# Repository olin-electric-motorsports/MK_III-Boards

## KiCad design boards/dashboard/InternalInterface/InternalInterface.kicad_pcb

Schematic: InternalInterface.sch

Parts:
J1: micromatch_female_TOP_ENTRY_locking_10; micromatch_female_vert_10; MPN A99504CT-ND
J2, J3: Ultrafit_2; MPN WM11570-ND
J4, J5, J6: Ultrafit_4; MPN WM11574-ND
R1: R_200; R_0805_OEM; MPN RMCF0805JT200RCT-ND

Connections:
+5V: J1.1, J1.8, J4.1, J5.1, J6.1, R1.2
AMS: J1.4, J2.1
GND: J1.2, J1.5, J1.7, J2.2, J3.2, J4.2, J5.2, J6.4
IMD: J1.6, J3.1
unnamed: J6.3, R1.1
SCL: J1.10, J4.4, J5.4
SDA: J1.9, J4.3, J5.3
START: J1.3, J6.2

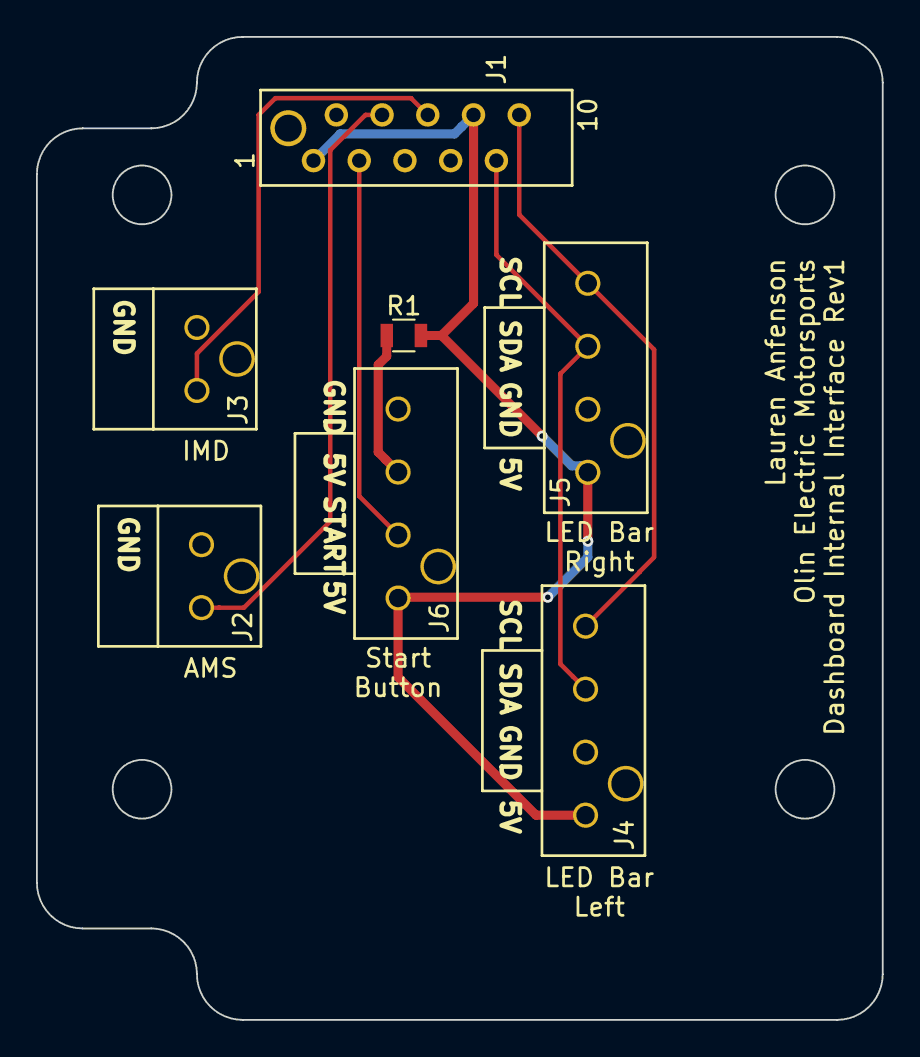
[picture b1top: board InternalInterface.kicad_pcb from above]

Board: 2 copper layers, 47.0 x 54.6 mm, 7 parts (0 on the bottom side), 8 nets.

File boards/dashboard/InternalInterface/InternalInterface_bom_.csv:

Component,Description,Part,References,Value,Footprint,Quantity Per PCB,Datasheet,Package,MPN,MFN,PurchasingLink,PurchasingLink2,MPN2
1,ULTRAFIT CONN HDR 02CKT,Ultrafit_2,J2 J3,Ultrafit_2,Ultrafit_2,2,,Value,WM11570-ND,Digi-Key,https://www.digikey.com/product-detail/en/molex-llc/17228611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,,
2,Ultrafit 4 Pin Connector,Ultrafit_4,J4 J5 J6,Ultrafit_4,Ultrafit_4,3,http://www.literature.molex.com/SQLImages/kelmscott/Molex/PD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,Value,WM11574-ND,Digi-Key,https://www.digikey.com/products/en?keywords=WM11574-ND,https://www.digikey.com/product-detail/en/molex-llc/17225610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,WM11564-ND
3,CONN FMALE-ON-BRD 10POS VERT T/H,micromatch_female_TOP_ENTRY_locking_10,J1,micromatch_female_TOP_ENTRY_locking_10,micromatch_female_vert_10,1,http://www.te.com/commerce/DocumentDelivery/DDEController?Ac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,Value,A99504CT-ND,Digi-Key,https://www.digikey.com/product-detail/en/te-connectivity-am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,,
4,Res 200 5%,R_200,R1,R_200,R_0805_OEM,1,https://www.seielect.com/Catalog/SEI-RMCF_RMCP.pdf,Value,RMCF0805JT200RCT-ND,Digi-Key,https://www.digikey.com/products/en?keywords=RMCF0805JT200RCT-ND,,





Component Groups:,4
Component Count:,7
Fitted Components:,7
Number of PCBs:,1
Total components:,7
Schematic Version:,
Schematic Date:,
BoM Date:,Wed 21 Feb 2018 10:05:45 PM EST
Schematic Source:,/home/lanfenson/MK_III-Boards-master/boards/dashboard/InternalInterface/InternalInterface.sch
KiCad Version:,Eeschema 4.0.7-e2-6376~58~ubuntu16.04.1

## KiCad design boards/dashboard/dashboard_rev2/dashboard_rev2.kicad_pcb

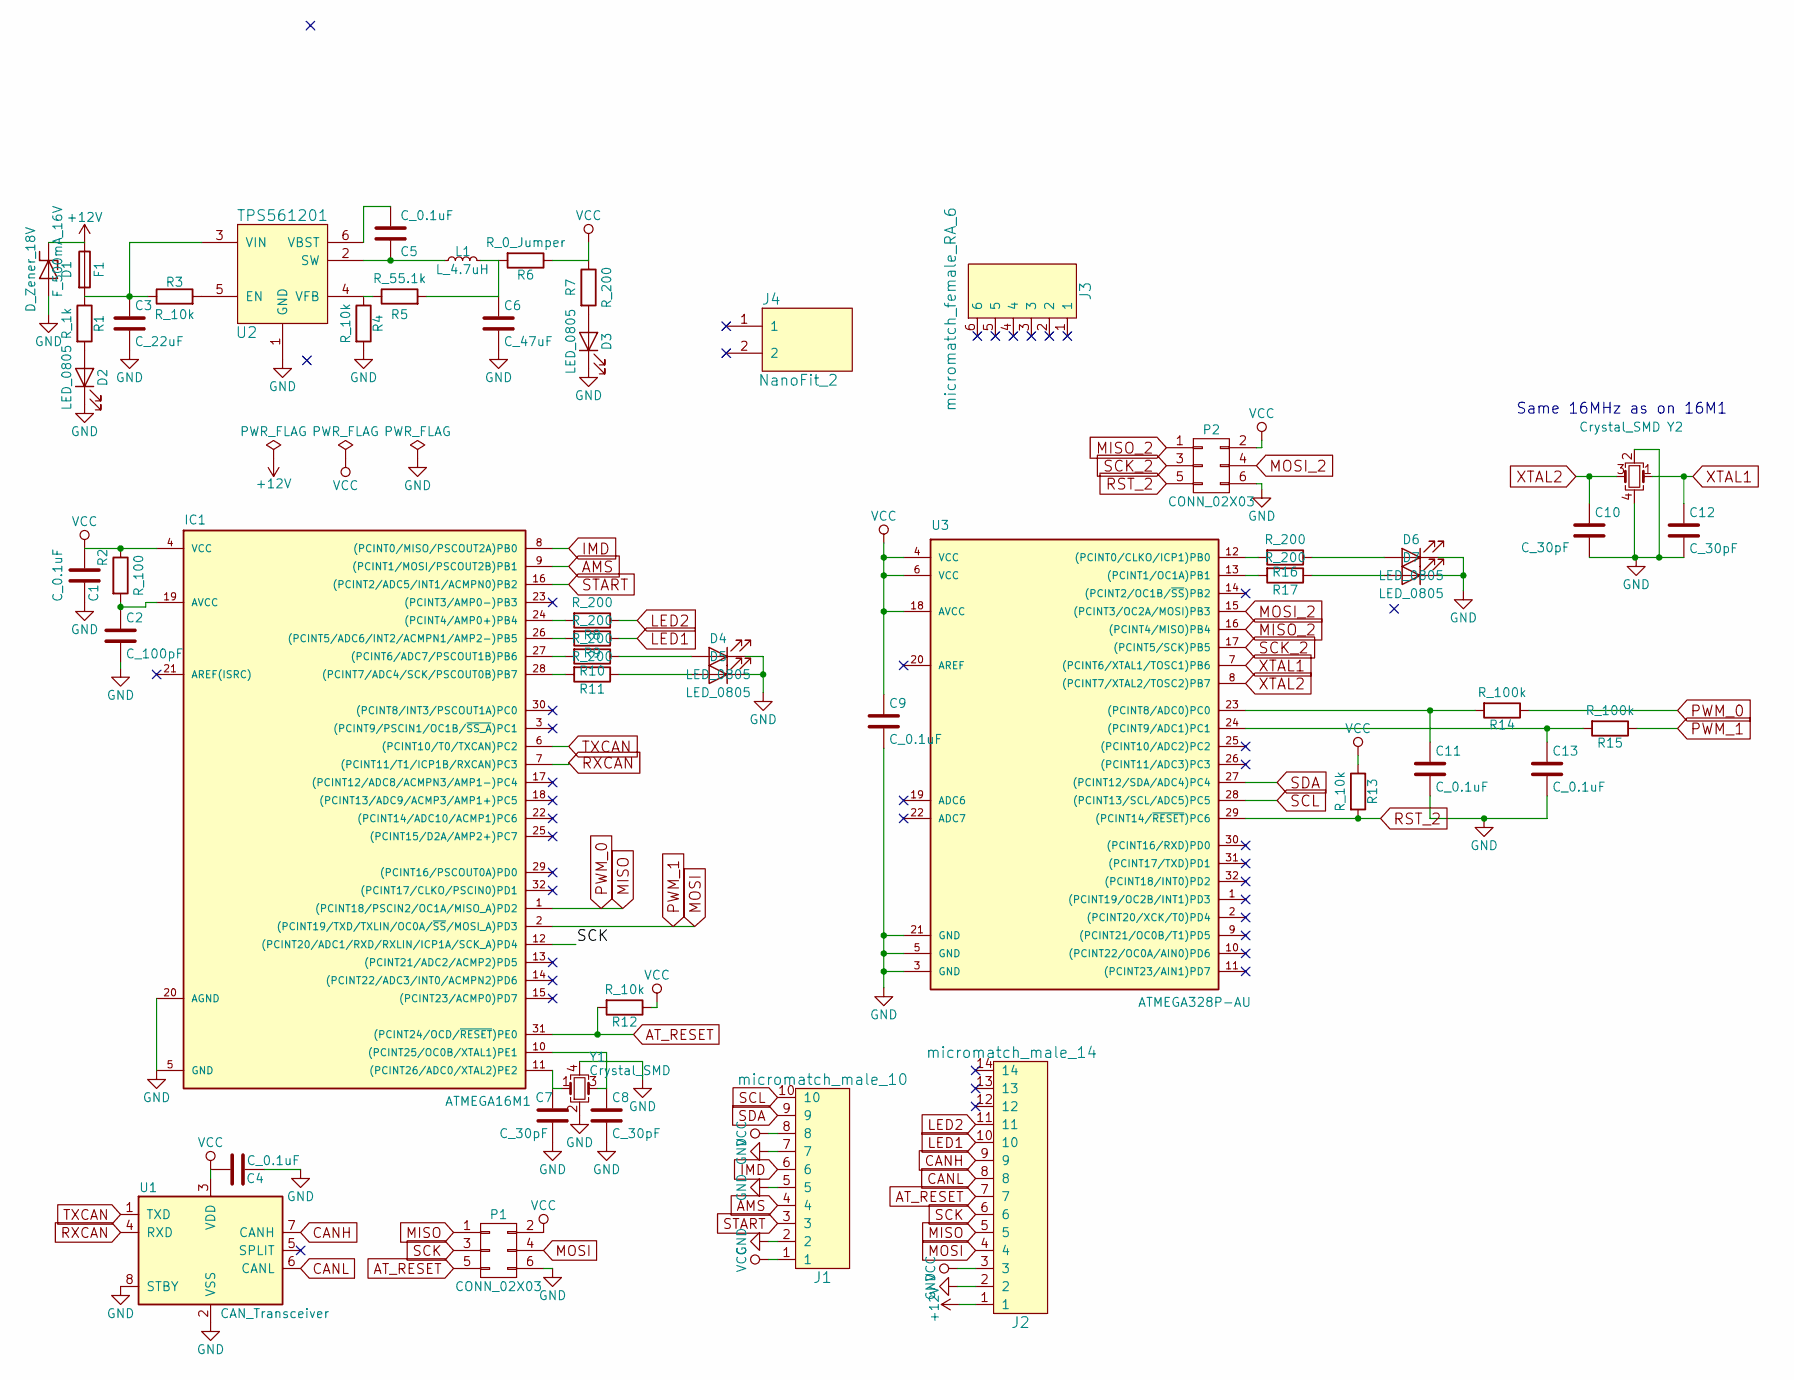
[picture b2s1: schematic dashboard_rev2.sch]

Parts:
C1, C4, C5: C_0.1uF; C_0805; MPN 478-3352-1-ND
C2: C_100pF; C_0805; MPN 399-1122-1-ND
C3: C_22uF; C_1206; MPN 1276-2725-1-ND
C6: C_47uF; C_0805; MPN 587-4280-1-ND
C7, C8: C_30pF; C_0805; MPN 1276-1130-1-ND
C9, C11, C13: C_0.1uF; C_0805_OEM; MPN 478-3352-1-ND
C10, C12: C_30pF; C_0805_OEM; MPN 1276-1130-1-ND
D1: D_Zener_18V; DO-214AA; MPN SMBJ5355B-TPMSCT-ND
D2, D3, D4, D5, D6, D7: LED_0805; MPN 475-1410-1-ND
F1: F_500mA_16V; Fuse_1210; MPN 507-1786-1-ND
IC1: ATMEGA16M1; TQFP-32_7x7mm_Pitch0.8mm; MPN ATMEGA16M1-AU-ND
J1: micromatch_male_10; micromatch_female_ra_10; MPN A110881CT-ND
J2: micromatch_male_14; micromatch_female_ra_14; MPN A99442CT-ND
J3: micromatch_female_RA_6; micromatch_female_ra_6; MPN A99483CT-ND
J4: NanoFit_2; OLIN_O
L1: L_4.7uH; 4.7uH_Inductor_OEM; MPN 445-6583-1-ND
P1, P2: CONN_02X03; Pin_Header_Straight_2x03; MPN 609-3234-ND
R1: R_1k; R_0805_OEM; MPN RNCP0805FTD1K00CT-ND
R2: R_100; R_0805; MPN RNCP0805FTD100RCT-ND
R3, R4, R12: R_10k; R_0805; MPN CRS0805-FX-1002ELFCT-ND
R5: R_55.1k; R_0805; MPN 311-51.1KCRCT-ND
R6: R_0_Jumper; R_2512; MPN A121322CT-ND
R7: R_200; R_0805; MPN RMCF0805JT200RCT-ND
R8, R9, R10, R11, R16, R17: R_200; R_0805_OEM; MPN RMCF0805JT200RCT-ND
R13: R_10k; R_0805_OEM; MPN CRS0805-FX-1002ELFCT-ND
R14, R15: R_100k; R_0805_OEM; MPN 311-100KCRCT-ND
U1: CAN_Transceiver; SOIC-8_3.9x4.9mm_Pitch1.27mm; MPN MCP2561-E/SN-ND
U2: TPS561201; SOT-23-6; MPN TPS561201
U3: ATMEGA328P-AU; TQFP-32_7x7mm_Pitch0.8mm
Y1, Y2: Crystal_SMD; Crystal_SMD_FA238; MPN SER3686CT-ND

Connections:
+12V: D1.1 (K), F1.1, J2.1
AMS: IC1.9 ((PCINT1/MOSI/PSCOUT2B)PB1), J1.4
AT_RESET: IC1.31 ((PCINT24/OCD/~RESET~)PE0), J2.7, P1.5, R12.2
CANH: J2.9, U1.7 (CANH)
CANL: J2.8, U1.6 (CANL)
GND: C1.2, C2.2, C3.2, C4.2, C6.2, C7.2, C8.2, C9.2, C10.2, C11.2, C12.2, C13.2, D1.2 (A), D2.1 (K), D3.1 (K), D4.1 (K), D5.1 (K), D6.1 (K), D7.1 (K), IC1.5 (GND), IC1.20 (AGND), J1.2, J1.5, J1.7, J2.2, P1.6, P2.6, R4.2, U1.2 (VSS), U1.8 (STBY), U2.1 (GND), U3.3 (GND), U3.5 (GND), U3.21 (GND), Y1.2, Y1.4, Y2.2, Y2.4
IMD: IC1.8 ((PCINT0/MISO/PSCOUT2A)PB0), J1.6
LED1: J2.10, R9.1
LED2: J2.11, R8.1
MISO: IC1.1 ((PCINT18/PSCIN2/OC1A/MISO_A)PD2), J2.5, P1.1, R14.1
MISO_2: P2.1, U3.16 ((PCINT4/MISO)PB4)
MOSI: IC1.2 ((PCINT19/TXD/TXLIN/OC0A/~SS~/MOSI_A)PD3), J2.4, P1.4, R15.1
MOSI_2: P2.4, U3.15 ((PCINT3/OC2A/MOSI)PB3)
unnamed: C2.1, IC1.19 (AVCC), R2.2
unnamed: C3.1, F1.2, R1.1, R3.1, U2.3 (VIN)
unnamed: C5.1, U2.6 (VBST)
unnamed: C5.2, L1.1, U2.2 (SW)
unnamed: C6.1, L1.2, R5.2, R6.2
unnamed: C7.1, IC1.11 ((PCINT26/ADC0/XTAL2)PE2), Y1.1
unnamed: C8.1, IC1.10 ((PCINT25/OC0B/XTAL1)PE1), Y1.3
unnamed: C11.1, R14.2, U3.23 ((PCINT8/ADC0)PC0)
unnamed: C13.1, R15.2, U3.24 ((PCINT9/ADC1)PC1)
unnamed: D2.2 (A), R1.2
unnamed: D3.2 (A), R7.2
unnamed: D4.2 (A), R10.1
unnamed: D5.2 (A), R11.1
unnamed: D6.2 (A), R16.1
unnamed: D7.2 (A), R17.1
unnamed: IC1.24 ((PCINT4/AMP0+)PB4), R8.2
unnamed: IC1.26 ((PCINT5/ADC6/INT2/ACMPN1/AMP2-)PB5), R9.2
unnamed: IC1.27 ((PCINT6/ADC7/PSCOUT1B)PB6), R10.2
unnamed: IC1.28 ((PCINT7/ADC4/SCK/PSCOUT0B)PB7), R11.2
unnamed: R3.2, U2.5 (EN)
unnamed: R4.1, R5.1, U2.4 (VFB)
unnamed: R16.2, U3.12 ((PCINT0/CLKO/ICP1)PB0)
unnamed: R17.2, U3.13 ((PCINT1/OC1A)PB1)
RST_2: P2.5, R13.2, U3.29 ((PCINT14/~RESET~)PC6)
RXCAN: IC1.7 ((PCINT11/T1/ICP1B/RXCAN)PC3), U1.4 (RXD)
SCK: IC1.12 ((PCINT20/ADC1/RXD/RXLIN/ICP1A/SCK_A)PD4), J2.6, P1.3
SCK_2: P2.3, U3.17 ((PCINT5/SCK)PB5)
SCL: J1.10, U3.28 ((PCINT13/SCL/ADC5)PC5)
SDA: J1.9, U3.27 ((PCINT12/SDA/ADC4)PC4)
START: IC1.16 ((PCINT2/ADC5/INT1/ACMPN0)PB2), J1.3
TXCAN: IC1.6 ((PCINT10/T0/TXCAN)PC2), U1.1 (TXD)
VCC: C1.1, C4.1, C9.1, IC1.4 (VCC), J1.1, J1.8, J2.3, P1.2, P2.2, R2.1, R6.1, R7.1, R12.1, R13.1, U1.3 (VDD), U3.4 (VCC), U3.6 (VCC), U3.18 (AVCC)
XTAL1: C12.1, U3.7 ((PCINT6/XTAL1/TOSC1)PB6), Y2.1
XTAL2: C10.1, U3.8 ((PCINT7/XTAL2/TOSC2)PB7), Y2.3

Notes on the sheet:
Same 16MHz as on 16M1

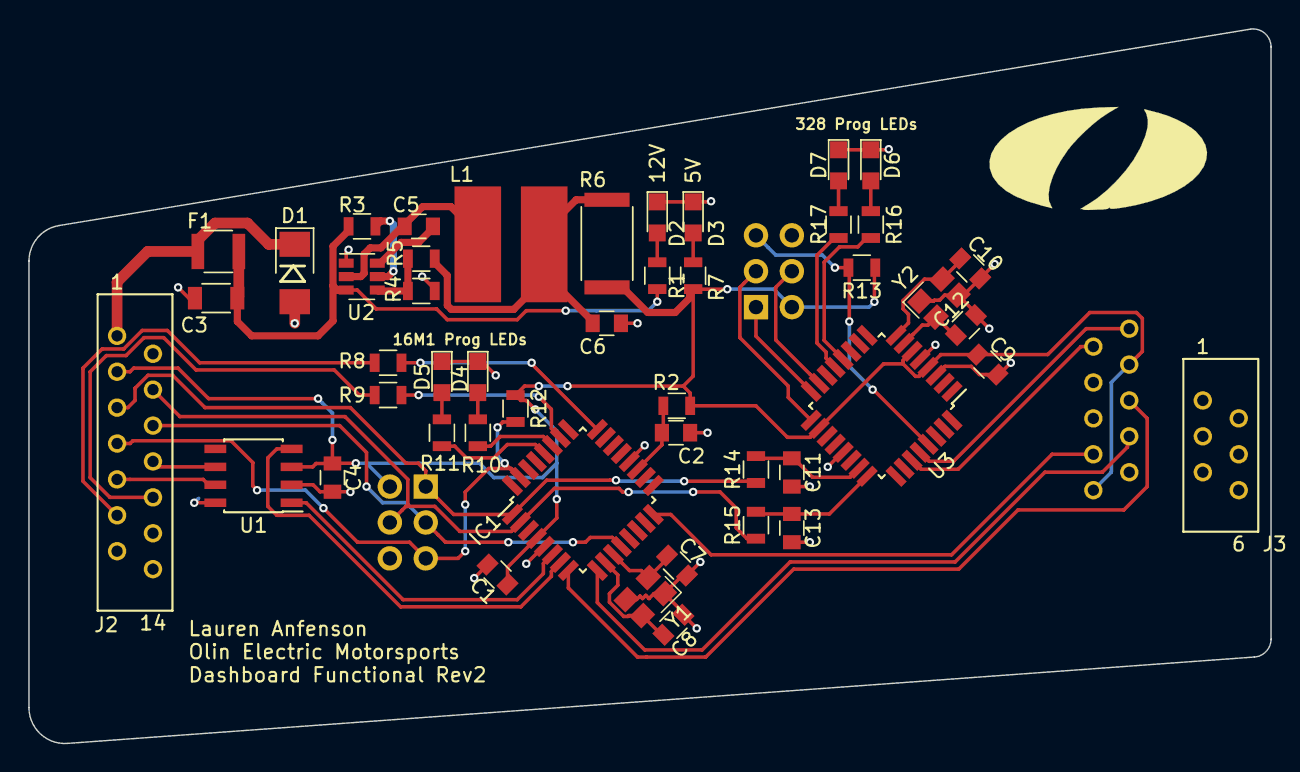
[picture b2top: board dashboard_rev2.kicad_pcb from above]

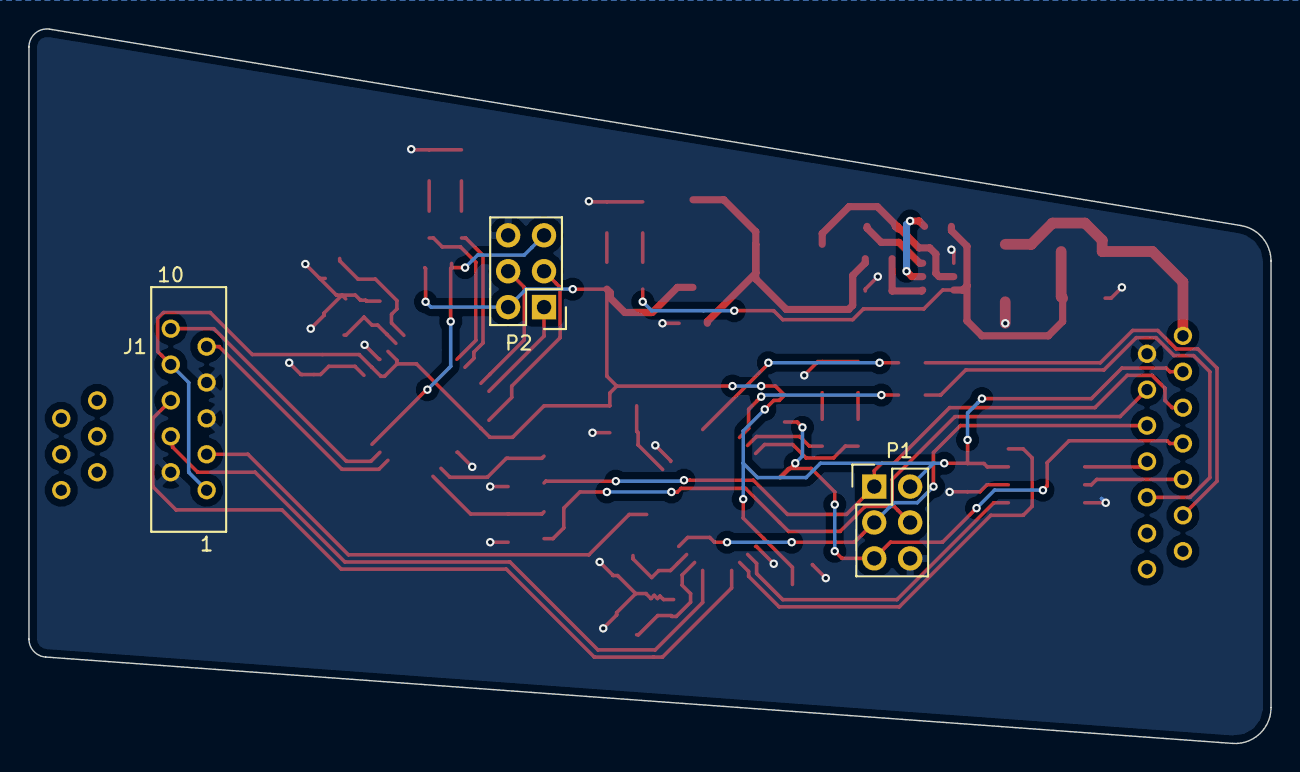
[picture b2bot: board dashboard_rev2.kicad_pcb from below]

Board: 2 copper layers, 87.9 x 50.6 mm, 51 parts (3 on the bottom side), 47 nets.

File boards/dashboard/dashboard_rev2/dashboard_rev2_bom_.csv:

Component,Description,Part,References,Value,Footprint,Quantity Per PCB,Datasheet,Package,MPN,MFN,PurchasingLink
1,Cap 50V 0.1uF 10% 0805,C_0.1uF,C1 C4 C5,C_0.1uF,C_0805,3,http://datasheets.avx.com/X7RDielectric.pdf,Value,478-3352-1-ND,Digi-Key,https://www.digikey.com/products/en?keywords=478-3352-1-ND
2,Cap 50V 0.1uF 10% 0805,C_0.1uF,C9 C11 C13,C_0.1uF,C_0805_OEM,3,http://datasheets.avx.com/X7RDielectric.pdf,Value,478-3352-1-ND,Digi-Key,https://www.digikey.com/products/en?keywords=478-3352-1-ND
3,Cap 50V 100pF 5% 0805,C_100pF,C2,C_100pF,C_0805,1,https://content.kemet.com/datasheets/KEM_C1003_C0G_SMD.pdf,Value,399-1122-1-ND,Digi-Key,https://www.digikey.com/product-detail/en/kemet/C0805C101J5G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
4,Unpolarized capacitor,C_22uF,C3,C_22uF,C_1206,1,http://www.samsungsem.com/kr/support/product-search/mlcc/__i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,Value,1276-2725-1-ND,Digi-Key,https://www.digikey.com/products/en?keywords=1276-2725-1-ND
5,Cap 50V 30pF 5% 0805,C_30pF,C10 C12,C_30pF,C_0805_OEM,2,https://media.digikey.com/pdf/Data%20Sheets/Samsung%20PDFs/C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,Value,1276-1130-1-ND,Digi-Key,https://www.digikey.com/product-detail/en/samsung-electro-me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
6,Cap 50V 30pF 5% 0805,C_30pF,C7 C8,C_30pF,C_0805,2,https://media.digikey.com/pdf/Data%20Sheets/Samsung%20PDFs/C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,Value,1276-1130-1-ND,Digi-Key,https://www.digikey.com/product-detail/en/samsung-electro-me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
7,CAP CER 47UF 6.3V X5R 0805,C_47uF,C6,C_47uF,C_0805,1,http://www.yuden.co.jp/productdata/catalog/en/mlcc_all_e.pdf,Value,587-4280-1-ND,Digi-Key,https://www.digikey.com/product-detail/en/taiyo-yuden/JMK212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
8,DIODE ZENER 18V 5W DO214AA,D_Zener_18V,D1,D_Zener_18V,DO-214AA,1,http://www.mccsemi.com/up_pdf/SMBJ5338B-SMBJ5388B(SMB).pdf,DO-214AA (SMB),SMBJ5355B-TPMSCT-ND,Digi-Key,https://www.digikey.com/products/en?keywords=SMBJ5355B-TPMSCT-ND
9,LED_0805,LED_0805,D2 D3 D4 D5 D6 D7,LED_0805,LED_0805,6,http://www.osram-os.com/Graphics/XPic9/00078860_0.pdf,Value,475-1410-1-ND,Digi-Key,https://www.digikey.com/products/en?keywords=475-1410-1-ND
10,PTC Fuse 16V 500mA,F_500mA_16V,F1,F_500mA_16V,Fuse_1210,1,https://belfuse.com/resources/CircuitProtection/datasheets/0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,Value,507-1786-1-ND,Digi-Key,https://www.digikey.com/product-detail/en/bel-fuse-inc/0ZCH0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
11,"TQFP32, 16k Flash, 1k SRAM, 512B EEPROM, CAN",ATMEGA16M1,IC1,ATMEGA16M1,TQFP-32_7x7mm_Pitch0.8mm,1,http://www.atmel.com/Images/Atmel-8209-8-bit%20AVR%20ATmega1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,Value,ATMEGA16M1-AU-ND,Digi-Key,https://www.digikey.com/product-detail/en/atmel/ATMEGA16M1-A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
12,,NanoFit_2,J4,NanoFit_2,OLIN_O,1,,,,,
13,connector micromatch female RA 6,micromatch_female_RA_6,J3,micromatch_female_RA_6,micromatch_female_ra_6,1,,Value,A99483CT-ND,Digi-Key,https://www.digikey.com/product-detail/en/te-connectivity-am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
14,connector micromatch male 10,micromatch_male_10,J1,micromatch_male_10,micromatch_female_ra_10,1,,Value,A110881CT-ND,Digi-Key,https://www.digikey.com/product-detail/en/te-connectivity-am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
15,connector micromatch male 14,micromatch_male_14,J2,micromatch_male_14,micromatch_female_ra_14,1,,Value,A99442CT-ND,Digi-Key,https://www.digikey.com/product-detail/en/te-connectivity-am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
16,Inductor 4.7uH 4.4A,L_4.7uH,L1,L_4.7uH,4.7uH_Inductor_OEM,1,https://product.tdk.com/info/en/documents/wdcatalog/withdraw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,Value,445-6583-1-ND,Digi-Key,https://www.digikey.com/product-detail/en/tdk-corporation/VL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
17,"Connector, double row, 02x03",CONN_02X03,P1 P2,CONN_02X03,Pin_Header_Straight_2x03,2,http://portal.fciconnect.com/Comergent//fci/drawing/67996.pdf,Value,609-3234-ND,Digi-Key,https://www.digikey.com/product-detail/en/amphenol-fci/67997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
18,Res 0 2512 3W Jumper,R_0_Jumper,R6,R_0_Jumper,R_2512,1,http://www.te.com/commerce/DocumentDelivery/DDEController?Ac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,Value,A121322CT-ND,Digi-Key,https://www.digikey.com/products/en?keywords=A121322CT-ND
19,Res 100 1%,R_100,R2,R_100,R_0805,1,https://www.seielect.com/Catalog/SEI-rncp.pdf,Value,RNCP0805FTD100RCT-ND,Digi-Key,https://www.digikey.com/products/en?keywords=RNCP0805FTD100RCT-ND
20,Res 100k 1%,R_100k,R14 R15,R_100k,R_0805_OEM,2,http://www.yageo.com.tw/exep/pages/download/literatures/PYu-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,Value,311-100KCRCT-ND,Digi-Key,https://www.digikey.com/products/en?keywords=311-100KCRCT-ND
21,Res 10k 1%,R_10k,R3 R4 R12,R_10k,R_0805,3,http://www.bourns.com/data/global/pdfs/CRS.pdf,Value,CRS0805-FX-1002ELFCT-ND,Digi-Key,https://www.digikey.com/products/en?keywords=CRS0805-FX-1002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
22,Res 10k 1%,R_10k,R13,R_10k,R_0805_OEM,1,http://www.bourns.com/data/global/pdfs/CRS.pdf,Value,CRS0805-FX-1002ELFCT-ND,Digi-Key,https://www.digikey.com/products/en?keywords=CRS0805-FX-1002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
23,Res 1k 1%,R_1k,R1,R_1k,R_0805_OEM,1,https://www.seielect.com/Catalog/SEI-rncp.pdf,Value,RNCP0805FTD1K00CT-ND,Digi-Key,https://www.digikey.com/products/en?keywords=RNCP0805FTD1K00CT-ND
24,Res 200 5%,R_200,R8 R9 R10 R11 R16 R17,R_200,R_0805_OEM,6,https://www.seielect.com/Catalog/SEI-RMCF_RMCP.pdf,Value,RMCF0805JT200RCT-ND,Digi-Key,https://www.digikey.com/products/en?keywords=RMCF0805JT200RCT-ND
25,Res 200 5%,R_200,R7,R_200,R_0805,1,https://www.seielect.com/Catalog/SEI-RMCF_RMCP.pdf,Value,RMCF0805JT200RCT-ND,Digi-Key,https://www.digikey.com/products/en?keywords=RMCF0805JT200RCT-ND
26,Res 55.1k 1%,R_55.1k,R5,R_55.1k,R_0805,1,http://www.yageo.com.tw/exep/pages/download/literatures/PYu-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,Value,311-51.1KCRCT-ND,Digi-Key,https://www.digikey.com/products/en?keywords=311-51.1KCRCT-ND
27,"TQFP32, 16k Flash, 1kB SRAM, 512B EEPROM",ATMEGA328P-AU,U3,ATMEGA328P-AU,TQFP-32_7x7mm_Pitch0.8mm,1,http://www.atmel.com/images/atmel-8271-8-bit-avr-microcontro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,,,,
28,"High-Speed CAN Transceiver, 1Mbps, 5V supply, SPLIT pin, -40C to +125C, SOIC8 package",CAN_Transceiver,U1,CAN_Transceiver,SOIC-8_3.9x4.9mm_Pitch1.27mm,1,http://www.microchip.com/mymicrochip/filehandler.aspx?ddocna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,Value,MCP2561-E/SN-ND,Digi-Key,https://www.digikey.com/products/en?keywords=mcp2561-e%2Fsn
29,4.5V - 17V Input 1A Synchronous Buck Converter,TPS561201,U2,TPS561201,SOT-23-6,1,http://www.ti.com/lit/ds/symlink/tps561201.pdf,Value,TPS561201,Digi-Key,https://www.digikey.com/products/en?keywords=296-46928-1-ND
30,"Two pin crystal, two ground/package pins (pin2 and 3) small symbol",Crystal_SMD,Y1 Y2,Crystal_SMD,Crystal_SMD_FA238,2,https://support.epson.biz/td/api/doc_check.php?dl=brief_FA-2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,Value,SER3686CT-ND,Digi-Key,https://www.digikey.com/products/en?keywords=SER3686CT-ND





Component Groups:,30
Component Count:,51
Fitted Components:,51
Number of PCBs:,1
Total components:,51
Schematic Version:,
Schematic Date:,
BoM Date:,Wed 21 Feb 2018 10:09:42 PM EST
Schematic Source:,/home/lanfenson/MK_III-Boards-master/boards/dashboard/dashboard_rev2/dashboard_rev2.sch
KiCad Version:,Eeschema 4.0.7-e2-6376~58~ubuntu16.04.1

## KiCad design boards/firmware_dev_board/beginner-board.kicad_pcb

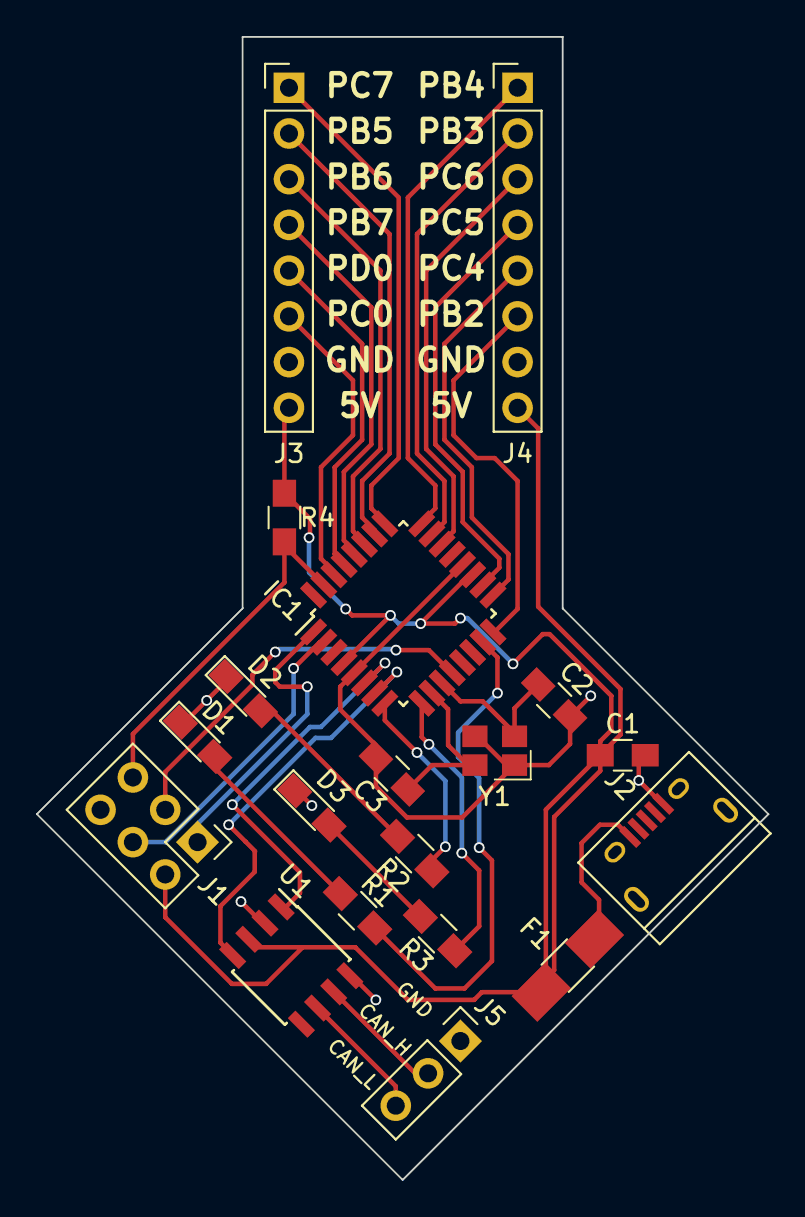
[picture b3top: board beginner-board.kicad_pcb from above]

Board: 2 copper layers, 40.6 x 63.5 mm, 19 parts (0 on the bottom side), 31 nets.

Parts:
C1: 0.1uF; C_0805_HandSoldering
C2, C3: 30pF; C_0805_HandSoldering
D1, D2, D3: LED; LED_0805_HandSoldering
F1: Polyfuse; Fuse_SMD1206_HandSoldering
IC1: ATMEGA16M1; TQFP-32_7x7mm_Pitch0.8mm
J1: CONN_02X03; Pin_Header_Straight_2x03_Pitch2.54mm
J2: USB_OTG; USB_Micro-B
J3, J4: CONN_01X08; Pin_Header_Straight_1x08_Pitch2.54mm
J5: CONN_01X03; Pin_Header_Straight_1x03_Pitch2.54mm
R1, R2, R3: 330; R_0805_HandSoldering
R4: 10K; R_0805_HandSoldering
U1: MCP2561-E/SN; SOIC-8_3.9x4.9mm_Pitch1.27mm
Y1: Crystal_SMD; Crystal_SMD_FA238

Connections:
16: IC1.16, J4.6
17: IC1.17, J4.5
18: IC1.18, J4.4
22: IC1.22, J4.3
23: IC1.23, J4.2
24: IC1.24, J4.1
25: IC1.25, J3.1
26: IC1.26, J3.2
27: IC1.27, J3.3
28: IC1.28, J3.4
29: IC1.29, J3.5
30: IC1.30, J3.6
/CANH: J5.2, U1.7
/CANL: J5.3, U1.6
GND: C1.2, C2.2, C3.2, D1.1, D2.1, D3.1, IC1.5, IC1.20, J1.6, J2.5, J2.6, J3.7, J4.7, J5.1, U1.2, U1.8, Y1.2, Y1.4
LED1: IC1.15, R1.1
LED2: IC1.8, R2.1
LED3: IC1.9, R3.1
MISO_A: IC1.1, J1.1
MOSI_A: IC1.2, J1.4
unnamed: C2.1, IC1.11, Y1.1
unnamed: C3.1, IC1.10, Y1.3
unnamed: D1.2, R1.2
unnamed: D2.2, R2.2
unnamed: D3.2, R3.2
unnamed: F1.2, J2.1
RESET: IC1.31, J1.5, R4.2
RXCAN: IC1.7, U1.4
SCK_A: IC1.12, J1.3
TXCAN: IC1.6, U1.1
VCC: C1.1, F1.1, IC1.4, IC1.19, J1.2, J3.8, J4.8, R4.1, U1.3

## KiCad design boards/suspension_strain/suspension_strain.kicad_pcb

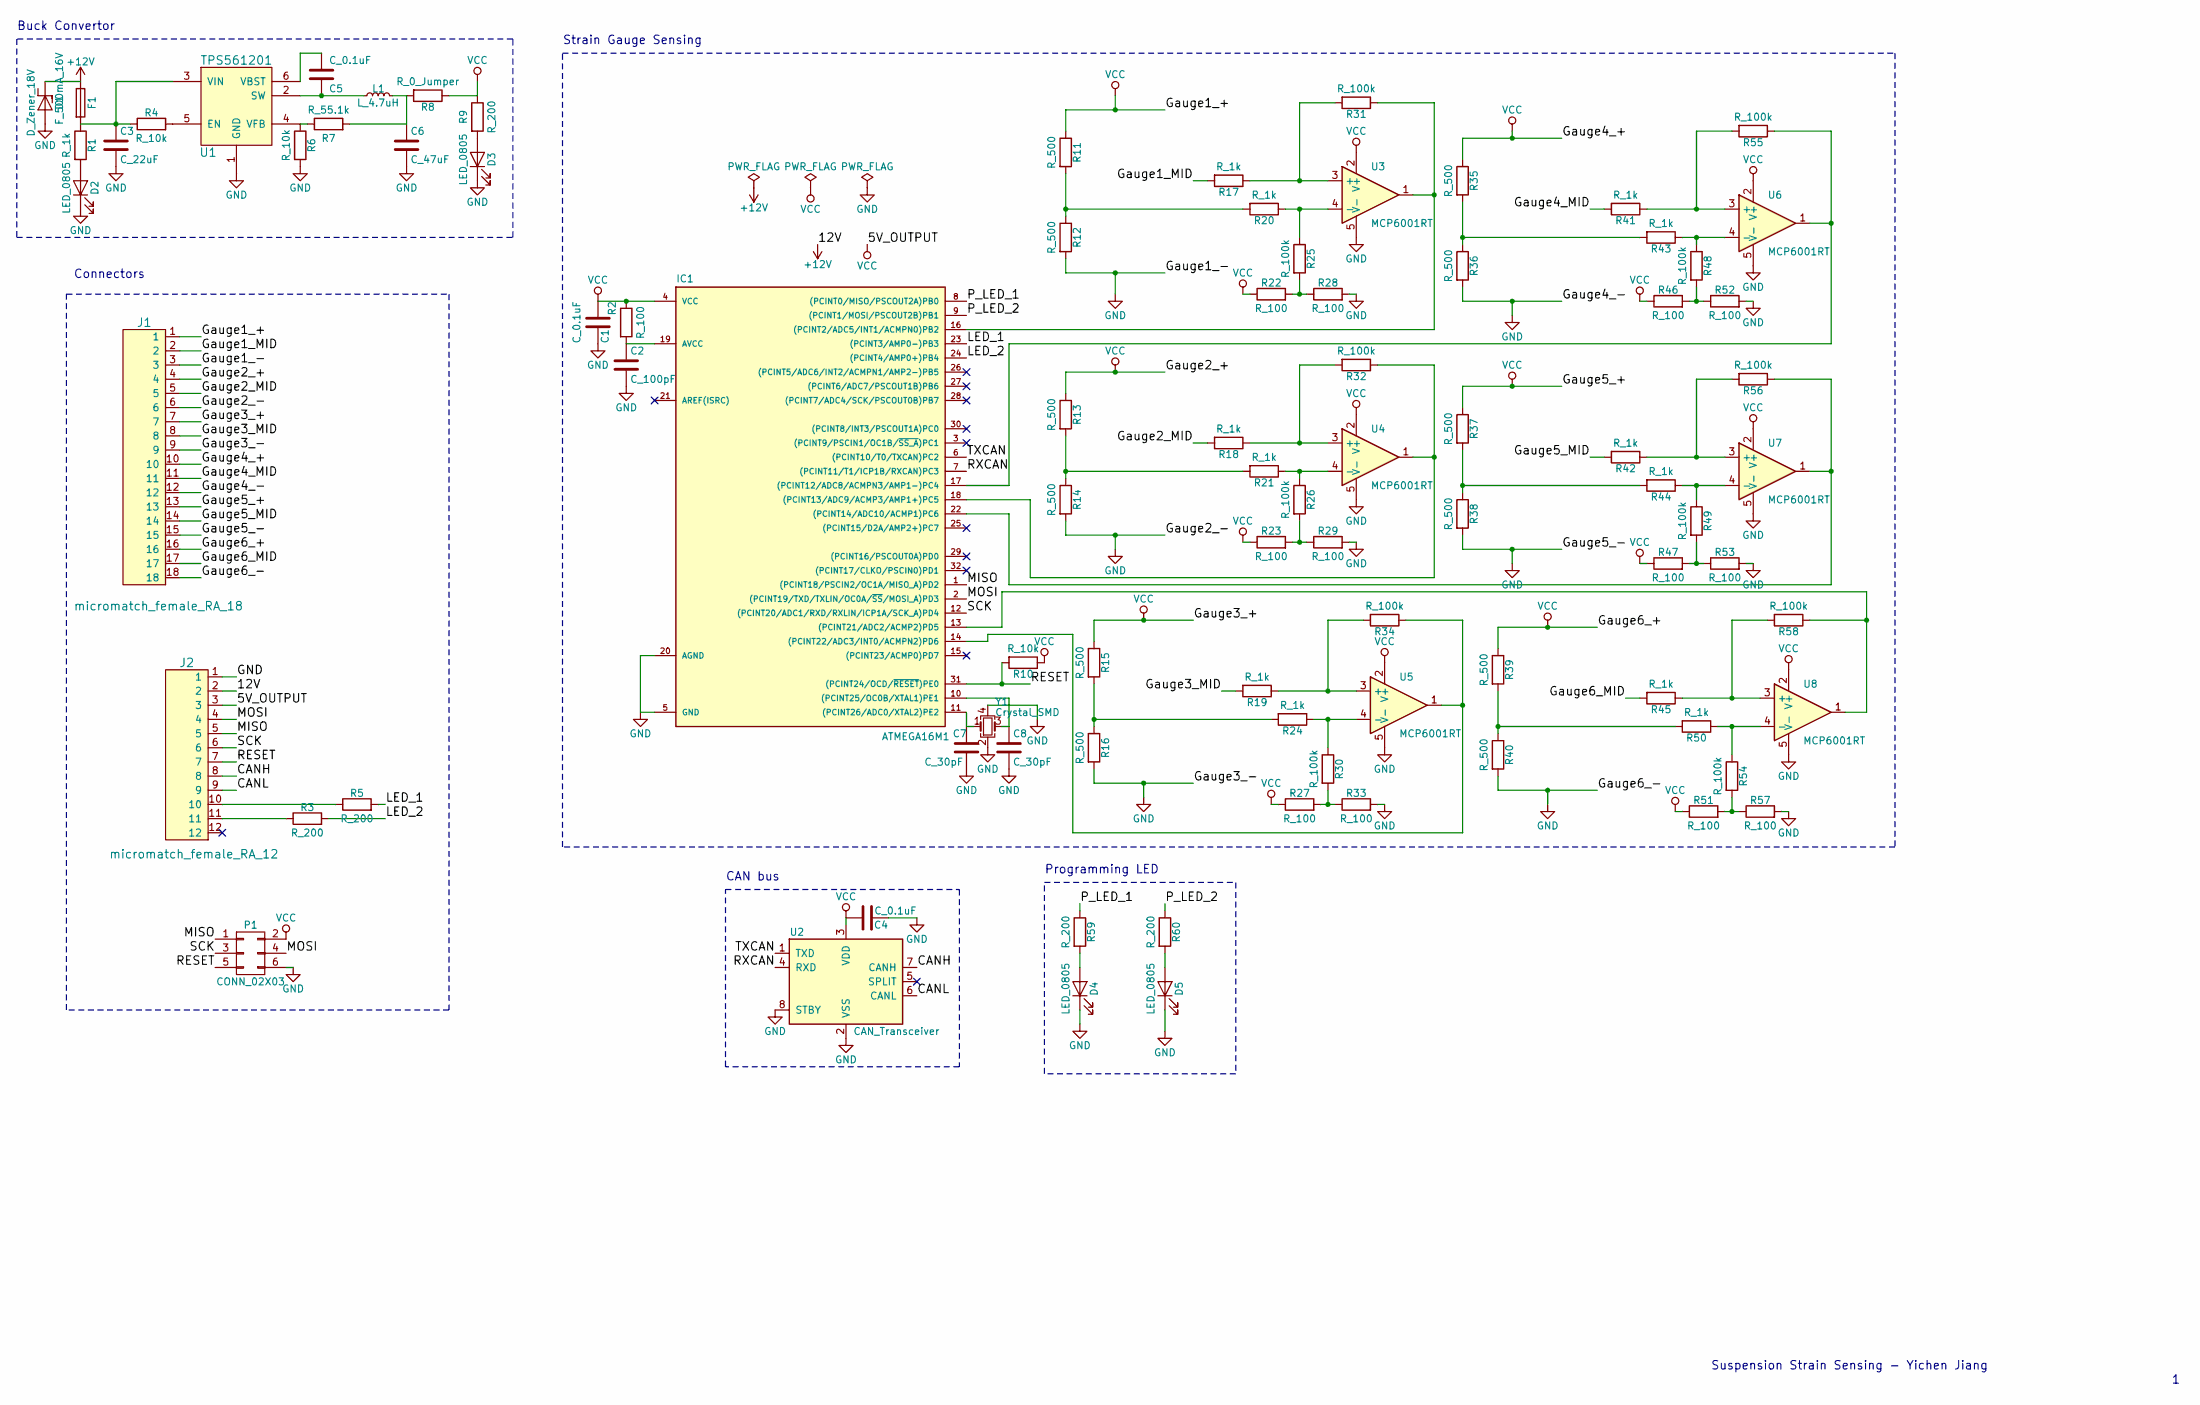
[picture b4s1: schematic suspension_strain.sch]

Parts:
C1, C4, C5: C_0.1uF; C_0805_OEM; MPN 478-3352-1-ND
C2: C_100pF; C_0805_OEM; MPN 399-1122-1-ND
C3: C_22uF; C_1206_OEM; MPN 1276-2725-1-ND
C6: C_47uF; C_0805_OEM; MPN 587-4280-1-ND
C7, C8: C_30pF; C_0805_OEM; MPN 1276-1130-1-ND
D1: D_Zener_18V; DO-214AA; MPN SMBJ5355B-TPMSCT-ND
D2, D3, D4, D5: LED_0805; LED_0805_OEM; MPN 475-1410-1-ND
F1: F_500mA_16V; Fuse_1210; MPN 507-1786-1-ND
IC1: ATMEGA16M1; TQFP-32_7x7mm_Pitch0.8mm; MPN ATMEGA16M1-AU-ND
J1: micromatch_female_RA_18; micromatch_female_ra_18; MPN A99489CT-ND
J2: micromatch_female_RA_12; micromatch_female_ra_12; MPN A99486CT-ND
L1: L_4.7uH; 4.7uH_Inductor_OEM; MPN 445-6583-1-ND
P1: CONN_02X03; Pin_Header_Straight_2x03; MPN 609-3234-ND
R1, R17, R18, R19, R20, R21, R24, R41, R42, R43, R44, R45, R50: R_1k; R_0805_OEM; MPN RNCP0805FTD1K00CT-ND
R2, R22, R23, R27, R28, R29, R33, R46, R47, R51, R52, R53, R57: R_100; R_0805_OEM; MPN RNCP0805FTD100RCT-ND
R3, R5, R9, R59, R60: R_200; R_0805_OEM; MPN RMCF0805JT200RCT-ND
R4, R6, R10: R_10k; R_0805_OEM; MPN CRS0805-FX-1002ELFCT-ND
R7: R_55.1k; R_0805_OEM; MPN 311-51.1KCRCT-ND
R8: R_0_Jumper; R_2512_OEM; MPN A121322CT-ND
R11, R12, R13, R14, R15, R16, R35, R36, R37, R38, R39, R40: R_500; R_0805_OEM; MPN 541-1905-2-ND
R25, R26, R30, R31, R32, R34, R48, R49, R54, R55, R56, R58: R_100k; R_0805_OEM; MPN 311-100KCRCT-ND
U1: TPS561201; SOT-23-6_OEM; MPN TPS561201
U2: CAN_Transceiver; SOIC-8_3.9x4.9mm_Pitch1.27mm_OEM; MPN MCP2561-E/SN-ND
U3, U4, U5, U6, U7, U8: MCP6001RT; SOT-23-5_OEM; MPN MCP6001RT-I/OTCT-ND
Y1: Crystal_SMD; Crystal_SMD_FA238; MPN SER3686CT-ND

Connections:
+12V: D1.1 (K), F1.1, J2.2
/CANH: J2.8, U2.7 (CANH)
/CANL: J2.9, U2.6 (CANL)
/Gauge1_MID: J1.2, R17.2
/Gauge2_MID: J1.5, R18.2
/Gauge3_MID: J1.8, R19.2
/Gauge4_MID: J1.11, R41.2
/Gauge5_MID: J1.14, R42.2
/Gauge6_MID: J1.17, R45.2
/LED_1: IC1.23 ((PCINT3/AMP0-)PB3), R5.2
/LED_2: IC1.24 ((PCINT4/AMP0+)PB4), R3.2
/MISO: IC1.1 ((PCINT18/PSCIN2/OC1A/MISO_A)PD2), J2.5, P1.1
/MOSI: IC1.2 ((PCINT19/TXD/TXLIN/OC0A/~SS~/MOSI_A)PD3), J2.4, P1.4
/P_LED_1: IC1.8 ((PCINT0/MISO/PSCOUT2A)PB0), R59.1
/P_LED_2: IC1.9 ((PCINT1/MOSI/PSCOUT2B)PB1), R60.1
/RESET: IC1.31 ((PCINT24/OCD/~RESET~)PE0), J2.7, P1.5, R10.2
/RXCAN: IC1.7 ((PCINT11/T1/ICP1B/RXCAN)PC3), U2.4 (RXD)
/SCK: IC1.12 ((PCINT20/ADC1/RXD/RXLIN/ICP1A/SCK_A)PD4), J2.6, P1.3
/TXCAN: IC1.6 ((PCINT10/T0/TXCAN)PC2), U2.1 (TXD)
GND: C1.2, C2.2, C3.2, C4.2, C6.2, C7.2, C8.2, D1.2 (A), D2.1 (K), D3.1 (K), D4.1 (K), D5.1 (K), IC1.5 (GND), IC1.20 (AGND), J1.3, J1.6, J1.9, J1.12, J1.15, J1.18, J2.1, P1.6, R6.2, R12.2, R14.2, R16.2, R28.2, R29.2, R33.2, R36.2, R38.2, R40.2, R52.2, R53.2, R57.2, U1.1 (GND), U2.2 (VSS), U2.8 (STBY), U3.5 (V-), U4.5 (V-), U5.5 (V-), U6.5 (V-), U7.5 (V-), U8.5 (V-), Y1.2, Y1.4
unnamed: C2.1, IC1.19 (AVCC), R2.2
unnamed: C3.1, F1.2, R1.1, R4.1, U1.3 (VIN)
unnamed: C5.1, U1.6 (VBST)
unnamed: C5.2, L1.1, U1.2 (SW)
unnamed: C6.1, L1.2, R7.2, R8.2
unnamed: C7.1, IC1.11 ((PCINT26/ADC0/XTAL2)PE2), Y1.1
unnamed: C8.1, IC1.10 ((PCINT25/OC0B/XTAL1)PE1), Y1.3
unnamed: D2.2 (A), R1.2
unnamed: D3.2 (A), R9.2
unnamed: D4.2 (A), R59.2
unnamed: D5.2 (A), R60.2
unnamed: IC1.13 ((PCINT21/ADC2/ACMP2)PD5), R58.1, U8.1
unnamed: IC1.14 ((PCINT22/ADC3/INT0/ACMPN2)PD6), R34.1, U5.1
unnamed: IC1.16 ((PCINT2/ADC5/INT1/ACMPN0)PB2), R31.1, U3.1
unnamed: IC1.17 ((PCINT12/ADC8/ACMPN3/AMP1-)PC4), R55.1, U6.1
unnamed: IC1.18 ((PCINT13/ADC9/ACMP3/AMP1+)PC5), R32.1, U4.1
unnamed: IC1.22 ((PCINT14/ADC10/ACMP1)PC6), R56.1, U7.1
unnamed: J2.10, R5.1
unnamed: J2.11, R3.1
unnamed: R4.2, U1.5 (EN)
unnamed: R6.1, R7.1, U1.4 (VFB)
unnamed: R11.2, R12.1, R20.2
unnamed: R13.2, R14.1, R21.2
unnamed: R15.2, R16.1, R24.2
unnamed: R17.1, R31.2, U3.3 (+)
unnamed: R18.1, R32.2, U4.3 (+)
unnamed: R19.1, R34.2, U5.3 (+)
unnamed: R20.1, R25.1, U3.4 (-)
unnamed: R21.1, R26.1, U4.4 (-)
unnamed: R22.2, R25.2, R28.1
unnamed: R23.2, R26.2, R29.1
unnamed: R24.1, R30.1, U5.4 (-)
unnamed: R27.2, R30.2, R33.1
unnamed: R35.2, R36.1, R43.2
unnamed: R37.2, R38.1, R44.2
unnamed: R39.2, R40.1, R50.2
unnamed: R41.1, R55.2, U6.3 (+)
unnamed: R42.1, R56.2, U7.3 (+)
unnamed: R43.1, R48.1, U6.4 (-)
unnamed: R44.1, R49.1, U7.4 (-)
unnamed: R45.1, R58.2, U8.3 (+)
unnamed: R46.2, R48.2, R52.1
unnamed: R47.2, R49.2, R53.1
unnamed: R50.1, R54.1, U8.4 (-)
unnamed: R51.2, R54.2, R57.1
VCC: C1.1, C4.1, IC1.4 (VCC), J1.1, J1.4, J1.7, J1.10, J1.13, J1.16, J2.3, P1.2, R2.1, R8.1, R9.1, R10.1, R11.1, R13.1, R15.1, R22.1, R23.1, R27.1, R35.1, R37.1, R39.1, R46.1, R47.1, R51.1, U2.3 (VDD), U3.2 (V+), U4.2 (V+), U5.2 (V+), U6.2 (V+), U7.2 (V+), U8.2 (V+)

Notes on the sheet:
CAN bus
Programming LED
Connectors
Buck Convertor
Strain Gauge Sensing
Suspension Strain Sensing - Yichen Jiang
